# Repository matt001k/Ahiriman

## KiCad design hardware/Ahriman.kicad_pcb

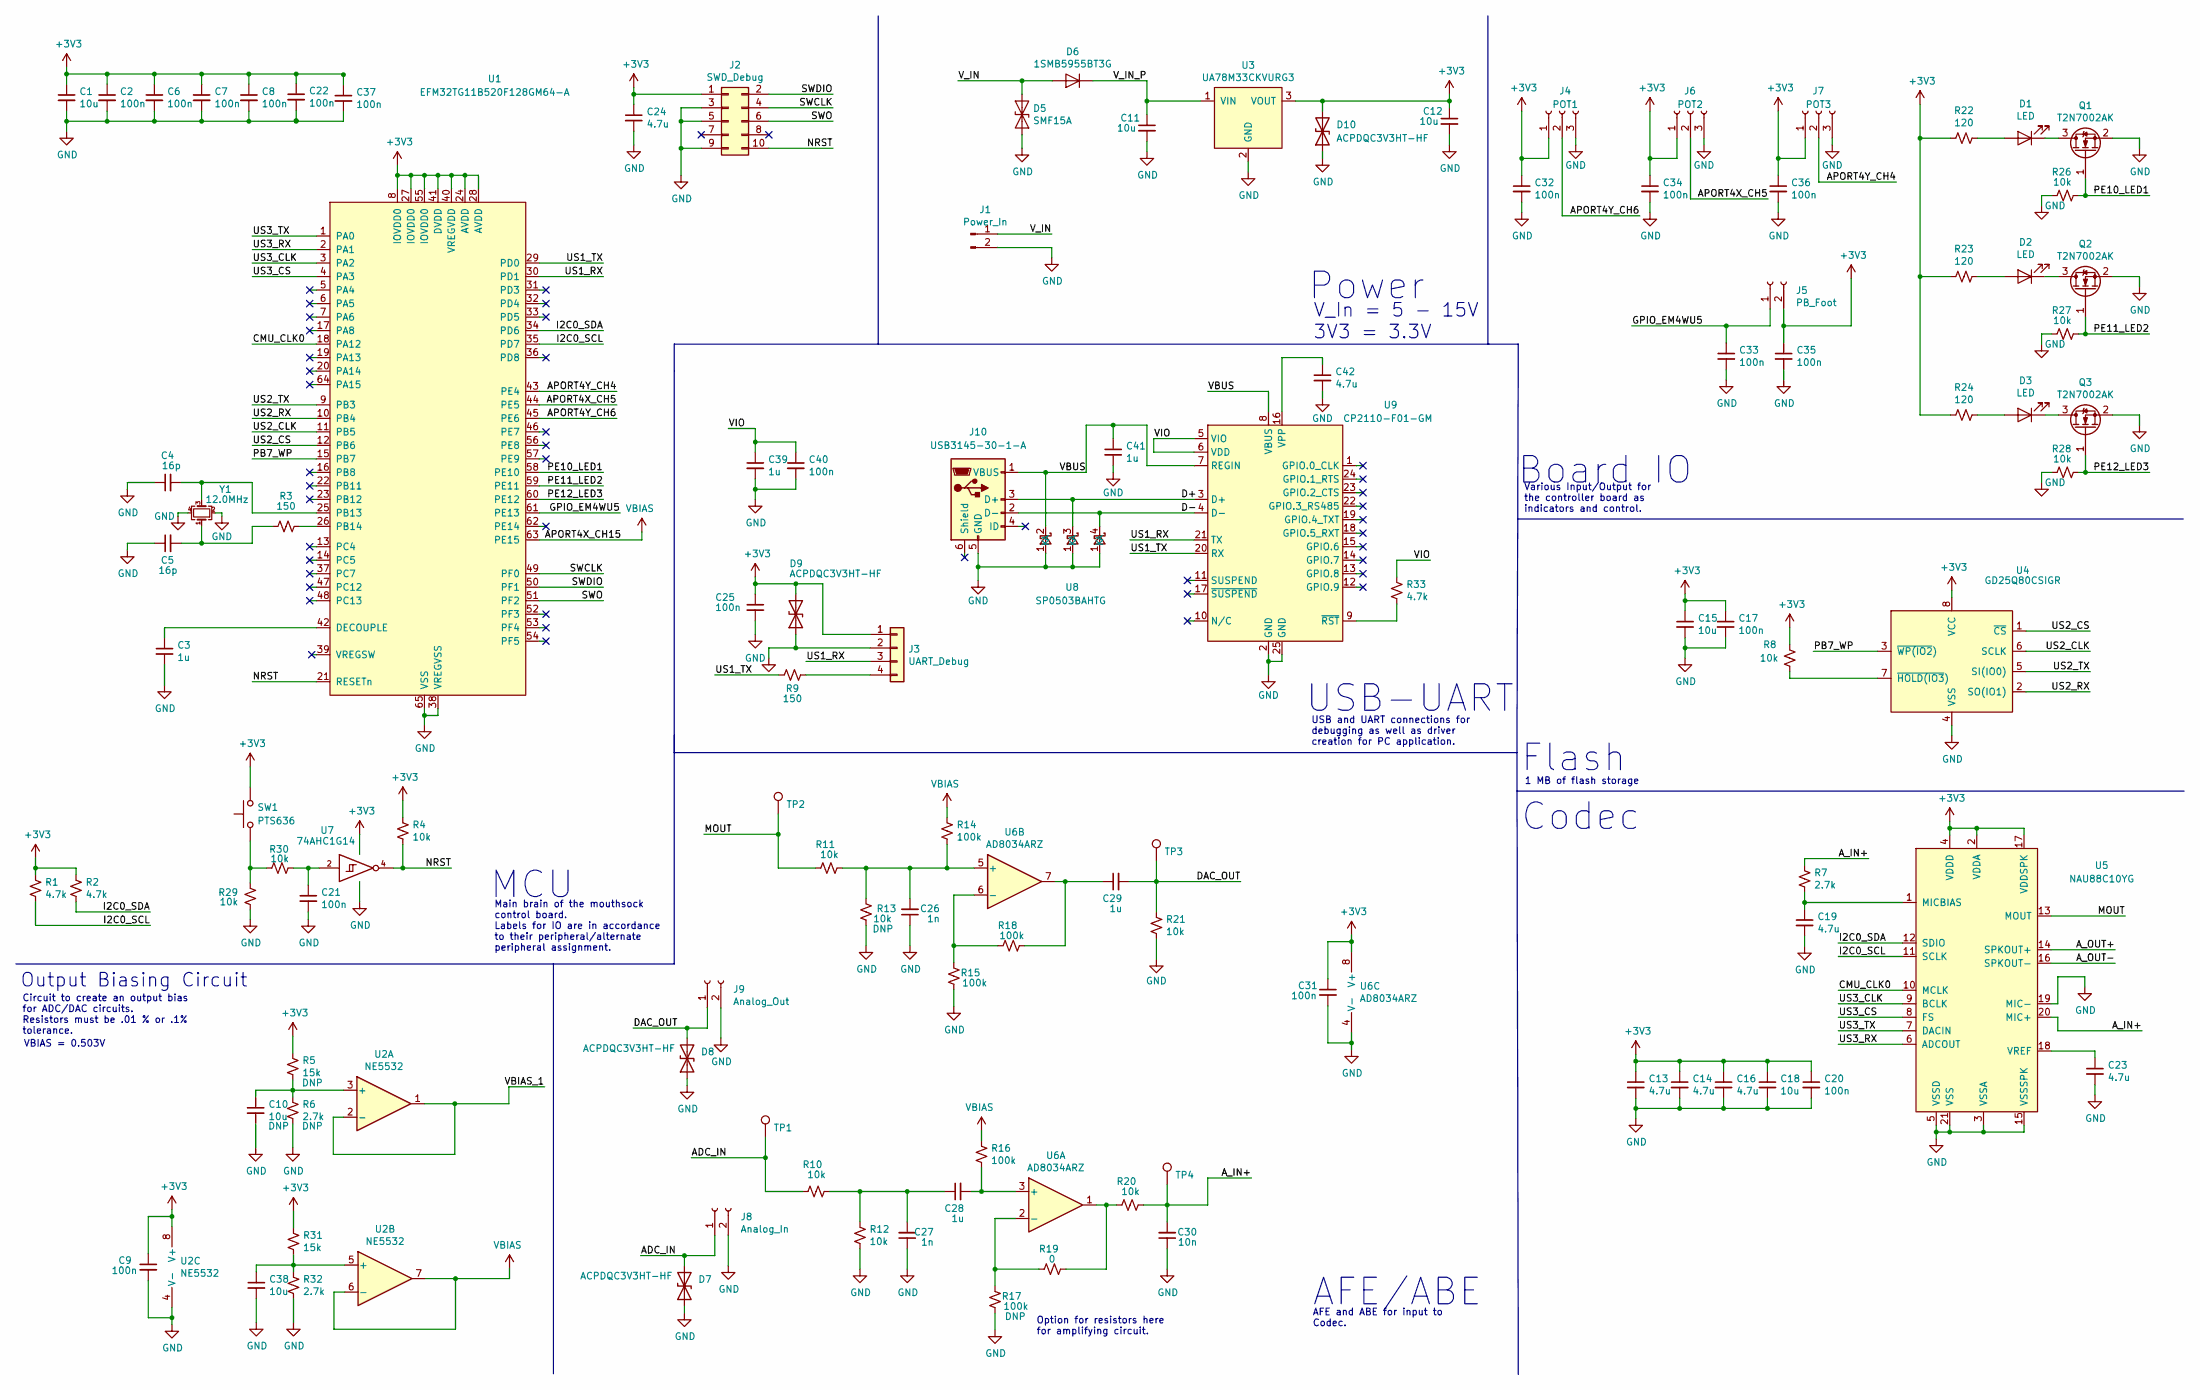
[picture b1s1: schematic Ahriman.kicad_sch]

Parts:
C1, C10, C15, C18, C38: 10u; C_0603_1608Metric
C2, C6, C7, C8, C9, C17, C20, C21, C25, C31, C32, C33, C34, C35, C36, C40: 100n; C_0603_1608Metric
C3, C28, C29, C39, C41: 1u; C_0603_1608Metric
C4, C5: 16p; C_0402_1005Metric
C11, C12: 10u; C_1206_3216Metric
C13, C14, C16, C19, C23, C24, C42: 4.7u; C_0603_1608Metric
C22, C37: 100n; C_0402_1005Metric
C26, C27: 1n; C_0603_1608Metric
C30: 10n; C_0603_1608Metric
D1, D2, D3: LED; LED_0805_2012Metric
D5: SMF15A; D_SOD-123F
D6: 1SMB5955BT3G; D_SMB
D7, D8, D9, D10: ACPDQC3V3HT-HF; D_0402_1005Metric
J1: Power_In; PinHeader_1x02_P2.54mm_Vertical
J2: SWD_Debug; PinHeader_2x05_P2.54mm_Vertical
J3: UART_Debug; PinHeader_1x04_P2.54mm_Vertical
J4: POT1; PinHeader_1x03_P2.54mm_Vertical
J5: PB_Foot; PinHeader_1x02_P2.54mm_Vertical
J6: POT2; PinHeader_1x03_P2.54mm_Vertical
J7: POT3; PinHeader_1x03_P2.54mm_Vertical
J8: Analog_In; PinHeader_1x02_P2.54mm_Vertical
J9: Analog_Out; PinHeader_1x02_P2.54mm_Vertical
J10: USB3145-30-1-A
Q1, Q2, Q3: T2N7002AK; SOT-23
R1, R2, R33: 4.7k; R_0603_1608Metric
R3, R9: 150; R_0402_1005Metric
R4, R8, R10, R11, R12, R13, R20, R21, R26, R27, R28, R29, R30: 10k; R_0603_1608Metric
R5, R31: 15k; R_0603_1608Metric
R6, R7, R32: 2.7k; R_0603_1608Metric
R14, R15, R16, R17, R18: 100k; R_0603_1608Metric
R19: 0; R_0603_1608Metric
R22, R23, R24: 120; R_0603_1608Metric
SW1: PTS636
TP1, TP2, TP3, TP4: TestPoint; TestPoint_Pad_D1.0mm
U1: EFM32TG11B520F128GM64-A; QFN-64-1EP_9x9mm_P0.5mm_EP7.3x7.3mm
U2: NE5532; SOIC-8_3.9x4.9mm_P1.27mm
U3: UA78M33CKVURG3; TO-252-3_TabPin2
U4: GD25Q80CSIGR; SOIC-8W_5.3x5.3mm_P1.27mm
U5: NAU88C10YG; QFN-20-1EP_4x4mm_P0.5mm_EP2.5x2.5mm
U6: AD8034ARZ; SOIC-8_3.9x4.9mm_P1.27mm
U7: 74AHC1G14; SOT-23-5
U8: SP0503BAHTG; SOT-143
U9: CP2110-F01-GM; QFN-24-1EP_4x4mm_P0.5mm_EP2.7x2.7mm
Y1: 12.0MHz; RH100-12.000-16-3030-TR; Part Number RH100-12.000-16-3030-TR

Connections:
+1V5: R14.1, R16.1, U1.63 (PE15), U2.6 (-), U2.7
+3V3: C1.1, C2.1, C6.1, C7.1, C8.1, C9.1, C12.1, C13.1, C14.1, C15.1, C16.1, C17.1, C18.1, C20.1, C22.1, C24.1, C25.1, C31.1, C32.1, C34.1, C35.1, C36.1, C37.1, D9.2 (A2), D10.2 (A2), J2.1, J3.1, J4.1, J5.2, J6.1, J7.1, R1.1, R2.1, R4.1, R5.1, R8.1, R22.2, R23.2, R24.2, R31.1, SW1.2, U1.8 (IOVDD0), U1.24 (AVDD), U1.27 (IOVDD0), U1.28 (AVDD), U1.40 (VREGVDD), U1.41 (DVDD), U1.55 (IOVDD0), U2.8 (V+), U3.3 (VOUT), U4.8 (VCC), U5.2 (VDDA), U5.4 (VDDD), U5.17 (VDDSPK), U6.8 (V+), U7.5 (VCC)
/ADC_IN: D7.2 (A2), J8.1, R10.1, TP1.1
/APORT4X_CH5: J6.2, U1.44 (PE5)
/APORT4Y_CH4: J7.2, U1.43 (PE4)
/APORT4Y_CH6: J4.2, U1.45 (PE6)
/A_IN+: C30.2, R7.1, R20.2, TP4.1, U5.20 (MIC+)
/A_OUT+: U5.14 (SPKOUT+)
/A_OUT-: U5.16 (SPKOUT-)
/CMU_CLK0: U1.18 (PA12), U5.10 (MCLK)
/D+: J10.3 (D+), U8.3 (K), U9.3 (D+)
/D-: J10.2 (D-), U8.4 (K), U9.4 (D-)
/DAC_OUT: C29.2, D8.2 (A2), J9.1, R21.1, TP3.1
/GPIO_EM4WU5: C33.1, J5.1, U1.61 (PE13)
/I2C0_SCL: R1.2, U1.35 (PD7), U5.11 (SCLK)
/I2C0_SDA: R2.2, U1.34 (PD6), U5.12 (SDIO)
/MOUT: R11.1, TP2.1, U5.13 (MOUT)
/NRST: J2.10, R4.2, U1.21 (RESETn), U7.4
/PB7_WP: U1.15 (PB7), U4.3 (~WP(IO2))
/PE10_LED1: Q1.1 (G), R26.2, U1.58 (PE10)
/PE11_LED2: Q2.1 (G), R27.2, U1.59 (PE11)
/PE12_LED3: Q3.1 (G), R28.2, U1.60 (PE12)
/SWCLK: J2.4, U1.49 (PF0)
/SWDIO: J2.2, U1.50 (PF1)
/SWO: J2.6, U1.51 (PF2)
/US1_RX: J3.3, U1.30 (PD1), U9.21 (TX)
/US1_TX: R9.2, U1.29 (PD0), U9.20 (RX)
/US2_CLK: U1.11 (PB5), U4.6 (SCLK)
/US2_CS: U1.12 (PB6), U4.1 (~CS)
/US2_RX: U1.10 (PB4), U4.2 (SO(IO1))
/US2_TX: U1.9 (PB3), U4.5 (SI(IO0))
/US3_CLK: U1.3 (PA2), U5.9 (BCLK)
/US3_CS: U1.4 (PA3), U5.8 (FS)
/US3_RX: U1.2 (PA1), U5.6 (ADCOUT)
/US3_TX: U1.1 (PA0), U5.7 (DACIN)
/VBIAS_1: U2.1, U2.2 (-)
/VBUS: C41.1, J10.1 (VBUS), U8.2 (K), U9.7 (REGIN), U9.8 (VBUS)
/VIO: C39.1, C40.1, R33.1, U9.5 (VIO), U9.6 (VDD)
/V_IN: D5.1 (A1), D6.2 (A), J1.1
/V_IN_P: C11.1, D6.1 (K), U3.1 (VIN)
GND: C1.2, C2.2, C3.2, C4.1, C5.1, C6.2, C7.2, C8.2, C9.2, C10.2, C11.2, C12.2, C13.2, C14.2, C15.2, C16.2, C17.2, C18.2, C19.2, C20.2, C21.2, C22.2, C23.2, C24.2, C25.2, C26.1, C27.1, C30.1, C31.2, C32.2, C33.2, C34.2, C35.2, C36.2, C37.2, C38.2, C39.2, C40.2, C41.2, C42.2, D5.2 (A2), D7.1 (A1), D8.1 (A1), D9.1 (A1), D10.1 (A1), J1.2, J2.3, J2.5, J2.9, J3.2, J4.3, J6.3, J7.3, J8.2, J9.2, J10.5 (GND), Q1.2 (S), Q2.2 (S), Q3.2 (S), R6.2, R12.2, R13.2, R15.1, R17.1, R21.2, R26.1, R27.1, R28.1, R29.2, R32.2, U1.38 (VREGVSS), U1.65 (VSS), U2.4 (V-), U3.2 (GND), U4.4 (VSS), U5.3 (VSSA), U5.5 (VSSD), U5.15 (VSSSPK), U5.19 (MIC-), U5.21 (VSS), U6.4 (V-), U7.3 (GND), U8.1 (A), U9.2 (GND), U9.25 (GND), Y1.2, Y1.4
unnamed: C3.1, U1.42 (DECOUPLE)
unnamed: C4.2, U1.25 (PB13), Y1.3
unnamed: C5.2, R3.2, Y1.1
unnamed: C10.1, R5.2, R6.1, U2.3 (+)
unnamed: C19.1, R7.2, U5.1 (MICBIAS)
unnamed: C21.1, R30.2, U7.2
unnamed: C23.1, U5.18 (VREF)
unnamed: C26.2, R11.2, R13.1, R14.2, U6.5 (+)
unnamed: C27.2, C28.1, R10.2, R12.1
unnamed: C28.2, R16.2, U6.3 (+)
unnamed: C29.1, R18.2, U6.7
unnamed: C38.1, R31.2, R32.1, U2.5 (+)
unnamed: C42.1, U9.16 (VPP)
unnamed: D1.1 (K), Q1.3 (D)
unnamed: D1.2 (A), R22.1
unnamed: D2.1 (K), Q2.3 (D)
unnamed: D2.2 (A), R23.1
unnamed: D3.1 (K), Q3.3 (D)
unnamed: D3.2 (A), R24.1
unnamed: J3.4, R9.1
unnamed: R3.1, U1.26 (PB14)
unnamed: R8.2, U4.7 (~HOLD(IO3))
unnamed: R15.2, R18.1, U6.6 (-)
unnamed: R17.2, R19.1, U6.2 (-)
unnamed: R19.2, R20.1, U6.1
unnamed: R29.1, R30.1, SW1.1
unnamed: R33.2, U9.9 (~RST)

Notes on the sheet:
Various Input/Output for the controller board as indicators and control.
Option for resistors here for amplifying circuit.
Power
MCU
AFE/ABE
Flash
V_In = 5 - 15V 3V3 = 3.3V
Main brain of the mouthsock control board. Labels for IO are in accordance to their peripheral/alternate peripheral assignment.
1 MB of flash storage
USB and UART connections for debugging as well as driver creation for PC application.
Circuit to create an output bias for ADC/DAC circuits. Resistors must be .01 % or .1% tolerance.
AFE and ABE for input to Codec.
USB-UART
Board IO
Codec
Output Biasing Circuit
VBIAS = 0.503V

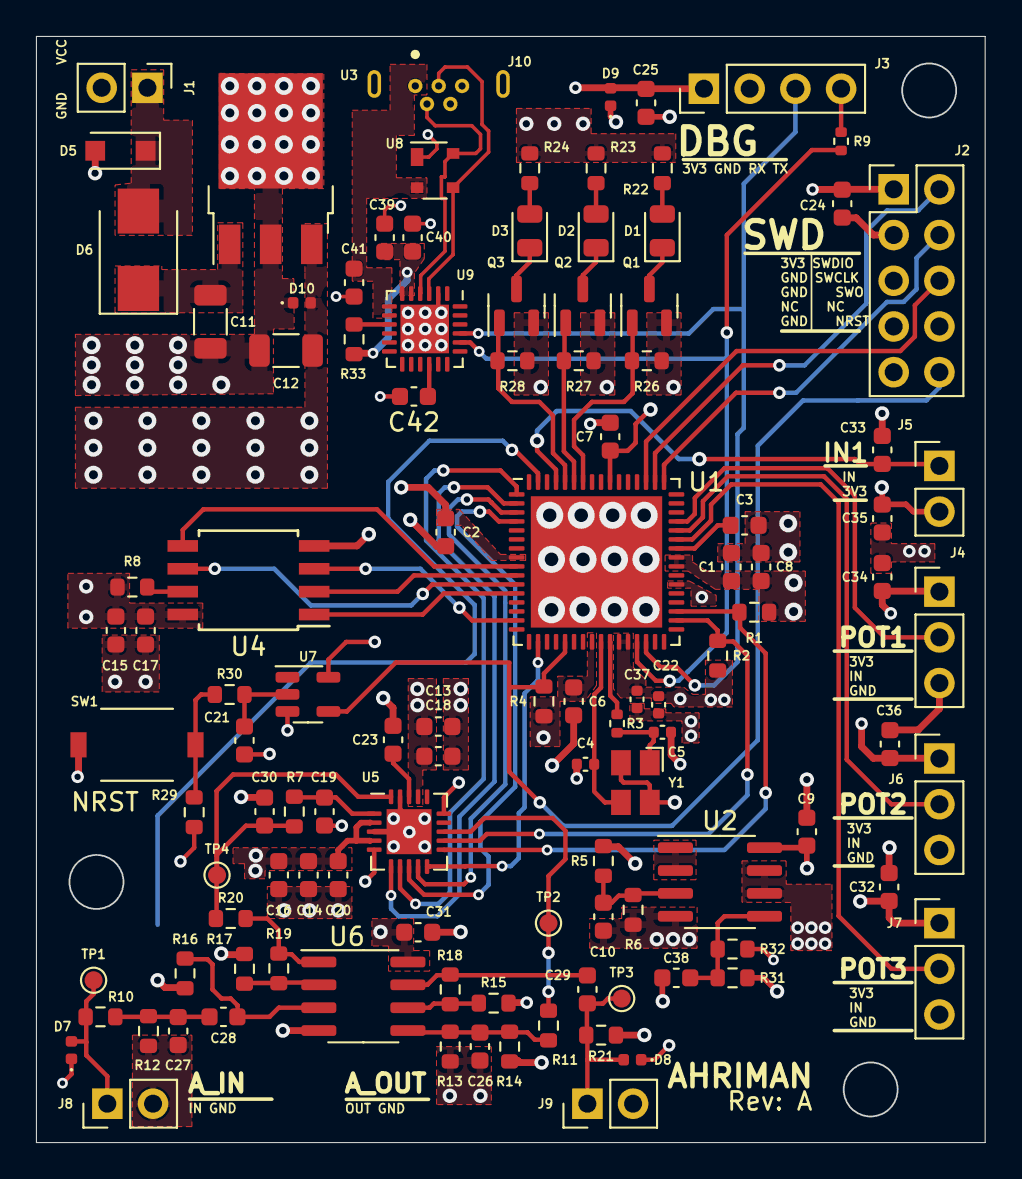
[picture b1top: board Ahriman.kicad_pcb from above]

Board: 4 copper layers, 52.7 x 61.5 mm, 111 parts (0 on the bottom side), 66 nets.

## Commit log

2022-08-15 Init Commit
    All files for Rev. A pushed
2022-08-25 Re-organize File Structure
    Start ignoring unwanted files
    Create BOM
    Re-organize files
2022-10-03 Firmware Initial Commit
    Sets up build system for initial project
2022-11-06 Initial Software Commit
    Adds terminal interface
    Adds bootloader interface
2022-11-10 Firmware Initial Commit
    Sets up build system for initial project
    Adds bootloader to project
    Adds simple application
2022-11-22 Adds I2C Driver
    Creates Flush, Transmit and Receive functionality for driver
2022-11-22 Updates Bootloader
    Creates more configurability in bootloader
2022-11-26 Adds Clock Output Updates I2C Driver
    Updates comments for I2C and SPI interfaces
2022-11-26 Set Up App Flashing/Debugging
    Allows debugging and flashing the application in accordance to loading the application from the bootloader
2022-12-08 Adds NAU88C10 Driver
    Adds NAU88C10 Dricver and full custom configuration
    Adds associated API needed
2022-12-08 I2S Driver Implementation
    Adds I2S driver and required API for application
